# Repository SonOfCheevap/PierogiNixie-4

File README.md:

# PierogiNixie-4
A Pi Pico powered nixie tube board that uses 4 IN-14 nixie tubes.

# Features
- Programmed using a Pi Pico
- ds3231m RTC
- CR2032 Battery for keeping time when off power
- 4x IN-14 Nixie Tubes
- 4x k155id1 Binary to Decimal decoders
- Onboard 12v to 5v Convertor

# Photos
Front

Back

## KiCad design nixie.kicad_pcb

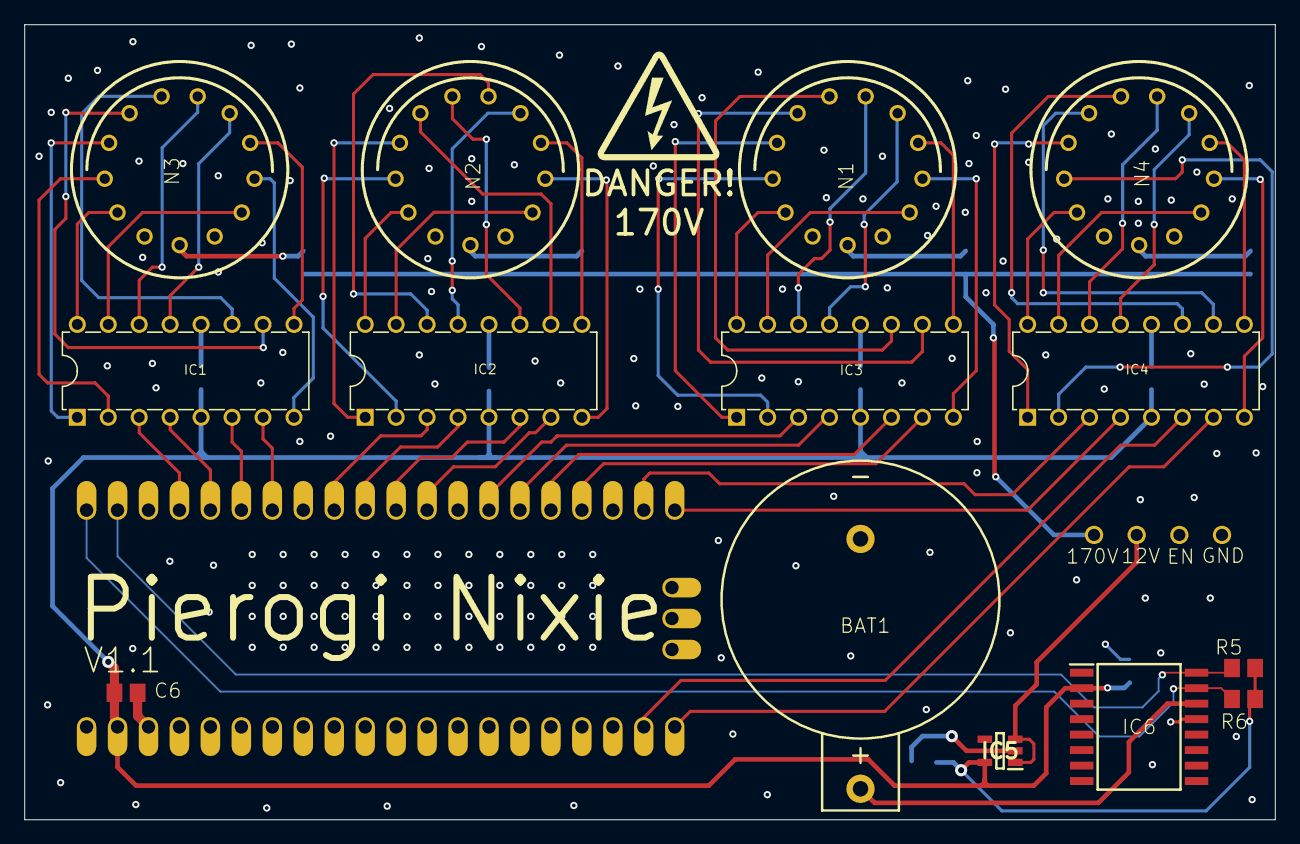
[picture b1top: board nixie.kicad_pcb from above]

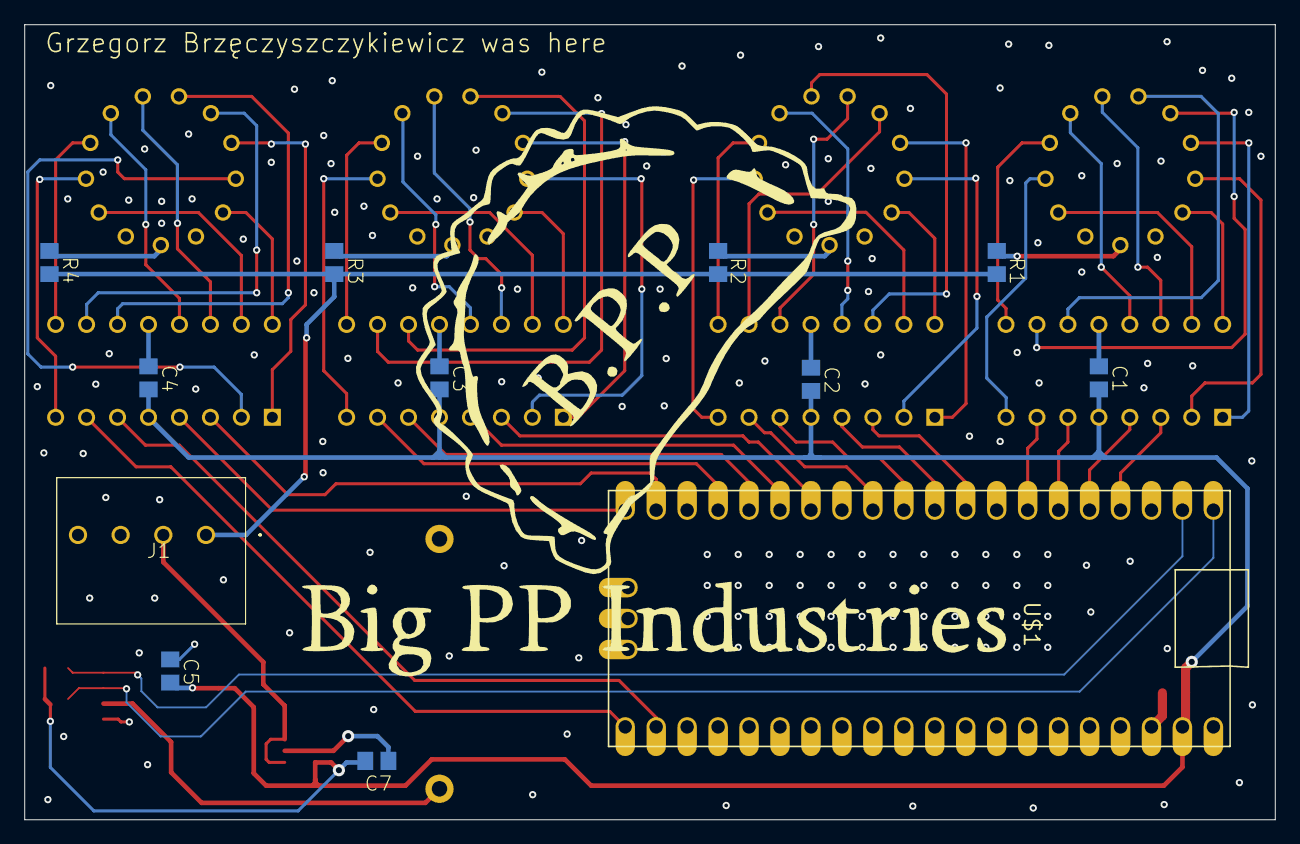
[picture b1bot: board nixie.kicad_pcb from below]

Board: 4 copper layers, 102.6 x 65.2 mm, 27 parts (16 on the bottom side), 67 nets.

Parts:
BAT1: SN2032
C1, C2, C3, C4, C5, C6: 100nf; C0805
C7: 470pf; C0805
IC1, IC2, IC3, IC4: SN74141; DIP16-2.54-19.2X7.62MM
IC5: MIC5219-5.0YM5-TR; SOT95P280X130-5N
IC6: DS3231M+TRL; SOIC127P1032X265-16N
J1: 1984989
N1, N2, N3, N4: Val**; IN-14
R1, R2, R3, R4, R5, R6: 10k; R0805
U$1: RPI_PICO-TH; RPI_PICO_TH
U$2: HVSMALL

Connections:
+5V: C1.1, C2.1, C3.1, C4.1, C5.1, C6.1, C7.1, IC1.5 (VCC), IC2.5 (VCC), IC3.5 (VCC), IC4.5 (VCC), IC5.5 (OUT), IC6.2 (VCC), R5.2, R6.2, U$1.VSYS
+12V: IC5.1 (IN), IC5.3 (EN), J1.2
/170V1: N1.A, R1.1
/170V2: N2.A, R2.1
/170V3: N3.A, R3.1
/170V4: N4.A, R4.1
/A1: IC1.3 (A), U$1.GP2
/A2: IC2.3 (A), U$1.GP6
/A3: IC3.3 (A), U$1.GP10
/A4: IC4.3 (A), U$1.GP14
/B1: IC1.6 (B), U$1.GP4
/B2: IC2.6 (B), U$1.GP8
/B3: IC3.6 (B), U$1.GP12
/B4: IC4.6 (B), U$1.GP17
/C1: IC1.7 (C), U$1.GP5
/C2: IC2.7 (C), U$1.GP9
/C3: IC3.7 (C), U$1.GP13
/C4: IC4.7 (C), U$1.GP16
/D1: IC1.4 (D), U$1.GP3
/D2: IC2.4 (D), U$1.GP7
/D3: IC3.4 (D), U$1.GP11
/D4: IC4.4 (D), U$1.GP15
/N10: IC1.16 (0), N1.0
/N11: IC1.15 (1), N1.1
/N12: IC1.8 (2), N1.2
/N13: IC1.9 (3), N1.3
/N14: IC1.13 (4), N1.4
/N15: IC1.14 (5), N1.5
/N16: IC1.11 (6), N1.6
/N17: IC1.10 (7), N1.7
/N18: IC1.1 (8), N1.8
/N19: IC1.2 (9), N1.9
/N20: IC2.16 (0), N2.0
/N21: IC2.15 (1), N2.1
/N22: IC2.8 (2), N2.2
/N23: IC2.9 (3), N2.3
/N24: IC2.13 (4), N2.4
/N25: IC2.14 (5), N2.5
/N26: IC2.11 (6), N2.6
/N27: IC2.10 (7), N2.7
/N28: IC2.1 (8), N2.8
/N29: IC2.2 (9), N2.9
/N30: IC3.16 (0), N3.0
/N31: IC3.15 (1), N3.1
/N32: IC3.8 (2), N3.2
/N33: IC3.9 (3), N3.3
/N34: IC3.13 (4), N3.4
/N35: IC3.14 (5), N3.5
/N36: IC3.11 (6), N3.6
/N37: IC3.10 (7), N3.7
/N38: IC3.1 (8), N3.8
/N39: IC3.2 (9), N3.9
/N40: IC4.16 (0), N4.0
/N41: IC4.15 (1), N4.1
/N42: IC4.8 (2), N4.2
/N43: IC4.9 (3), N4.3
/N44: IC4.13 (4), N4.4
/N45: IC4.14 (5), N4.5
/N46: IC4.11 (6), N4.6
/N47: IC4.10 (7), N4.7
/N48: IC4.1 (8), N4.8
/N49: IC4.2 (9), N4.9
/SCL: IC6.16 (SCL), R5.1, U$1.GP1
/SDA: IC6.15 (SDA), R6.1, U$1.GP0
GND: BAT1.-, C1.2, C2.2, C3.2, C4.2, C5.2, C6.2, C7.2, IC1.12 (GND), IC2.12 (GND), IC3.12 (GND), IC4.12 (GND), IC5.2 (GND), IC6.13 (GND), J1.4, U$1.AGND, U$1.GND@1 (GND), U$1.GND@2 (GND), U$1.GND@3 (GND), U$1.GND@4 (GND), U$1.GND@5 (GND), U$1.GND@6 (GND), U$1.GND@7 (GND), U$1.GND@8 (GND)
unnamed: BAT1.+, IC6.14 (VBAT)
VCC: J1.1, R1.2, R2.2, R3.2, R4.2

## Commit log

2023-06-06 Add files via upload
    Project files + Gerber
2023-06-23 Adding WIP files
2023-06-25 revert
2023-06-25 gitignore
2024-06-07 Create LICENSE
